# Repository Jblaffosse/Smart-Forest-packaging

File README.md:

# Smart-Forest-hardware

In this repository, you can find files for the shields, and also to manufacture the package thanks to the 3D printer.

## Solidwork files
- The solidwork files for the packaging and also the model of the weather station.

- You can find the two 3D stl files, one for the top and the other for the bottom.

## KiCAD files
You can find the two KiCAD project for the light sensor and the Temperature/Humidity sensor, they include:

- components needed for the shield.

- schematic of the shield.

- PCB of the shield.

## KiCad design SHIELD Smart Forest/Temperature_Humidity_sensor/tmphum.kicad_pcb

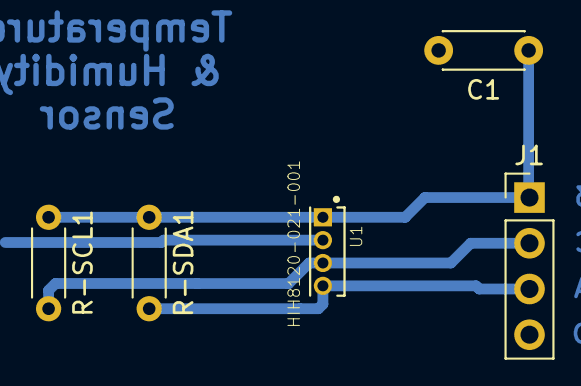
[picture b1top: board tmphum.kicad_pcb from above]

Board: 2 copper layers, 5 parts (0 on the bottom side), 4 nets.

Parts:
C1: 0.22u; C_Disc_D4.3mm_W1.9mm_P5.00mm
J1: Conn_01x04_Male; PinHeader_1x04_P2.54mm_Vertical
R-SCL1: 2.2k; R_Axial_DIN0204_L3.6mm_D1.6mm_P5.08mm_Horizontal
R-SDA1: 2.2k; R_Axial_DIN0204_L3.6mm_D1.6mm_P5.08mm_Horizontal
U1: HIH8120-021-001; SIP191W41P127L490H390Q4

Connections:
+3V3: C1.1, J1.1, R-SCL1.1, R-SDA1.1, U1.1
/SCL: J1.2, R-SCL1.2, U1.3
/SDA: J1.3, R-SDA1.2, U1.4
GND: C1.2, J1.4, U1.2

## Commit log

2019-01-16 Solidwork files
2019-01-16 Sensor shield Add KiCAD files
